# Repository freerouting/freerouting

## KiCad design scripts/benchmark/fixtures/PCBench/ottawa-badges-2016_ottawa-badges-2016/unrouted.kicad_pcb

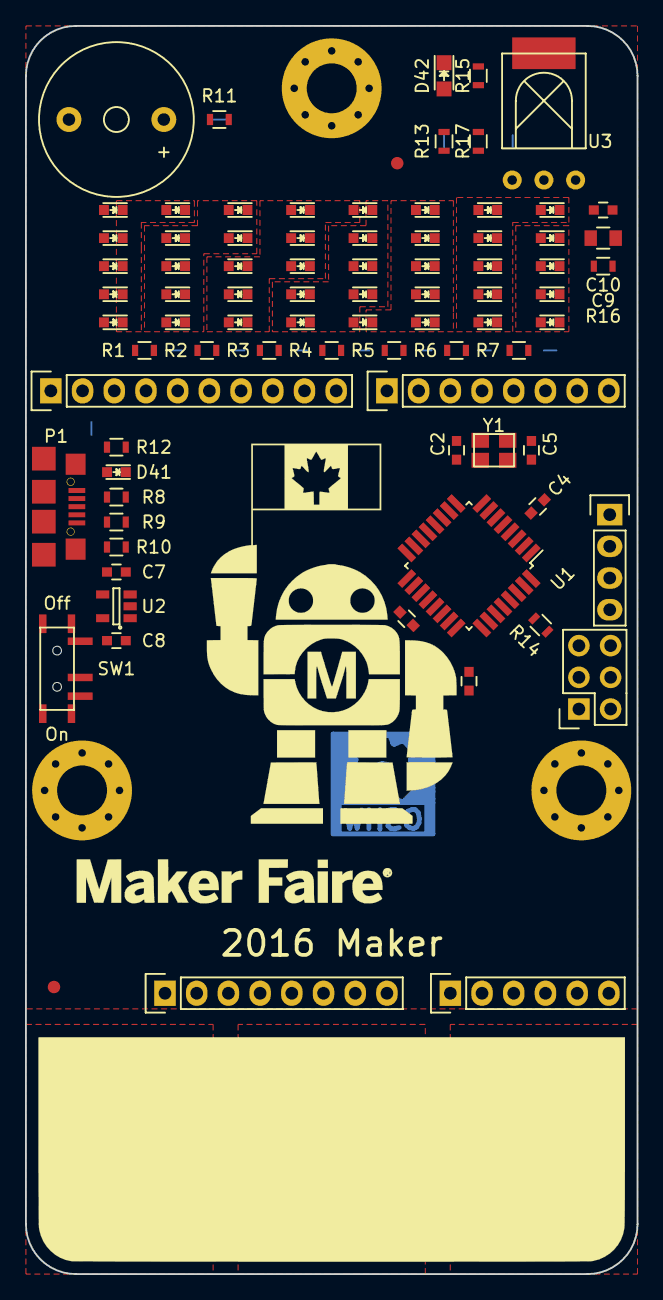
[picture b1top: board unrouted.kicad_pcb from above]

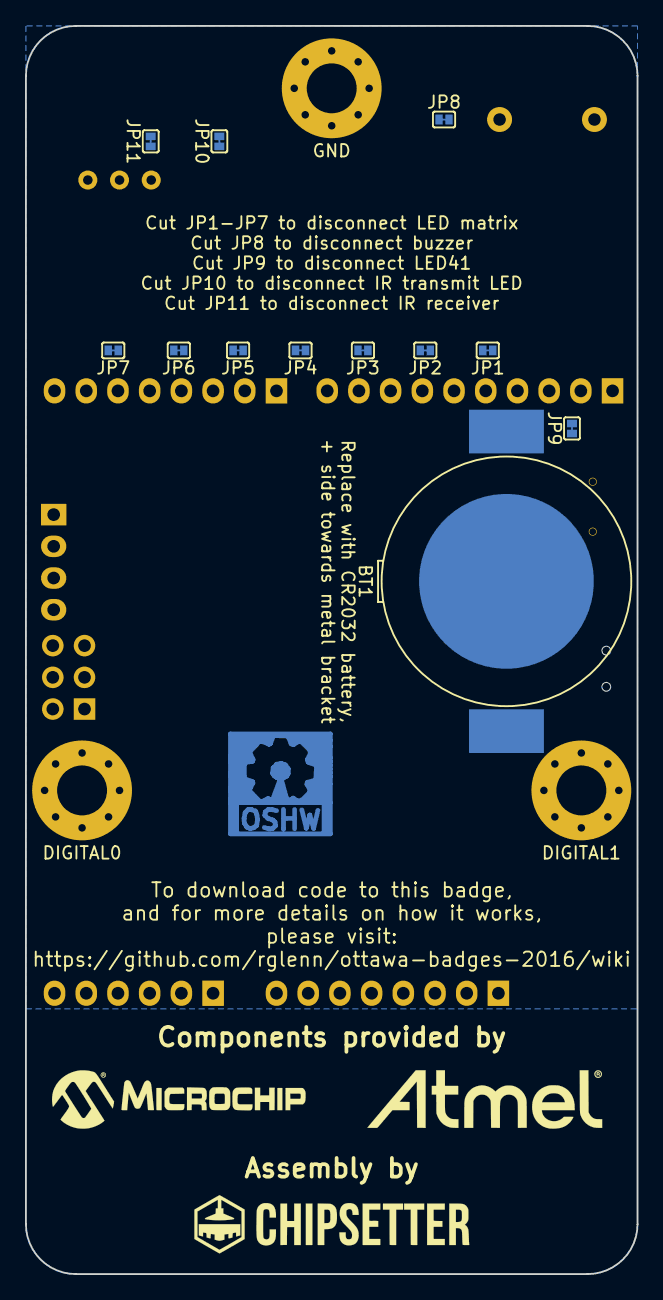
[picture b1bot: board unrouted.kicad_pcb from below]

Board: 2 copper layers, 49.0 x 100.0 mm, 96 parts (12 on the bottom side), 58 nets, no tracks yet.

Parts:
BT1: CR2032; CR2032-SHRAPNEL
C1, C4, C6, C10: 100n; C_0603
C2, C5: 18p; C_0603
C7, C8: 1u; C_0603
C9: 10u; C_0805
D1, D2, D3, D4, D5, D6, D7, D8, D9, D10, D11, D12, D13, D14, D15, D16, D17, D18, D19, D20, D21, D22, D23, D24, D25, D26, D27, D28, D29, D30, D31, D32, D33, D34, D35, D36, D37, D38, D39, D40, D41: Led_Small; LED_0603
D42: Led_Small; LED_0805
JP1, JP2, JP3, JP4, JP5, JP6, JP7, JP8, JP9, JP10, JP11: Jumper_NC_Small; SJ2
P1: USB_OTG; 10118192-0001LF
P2, P5: CONN_01X08; Socket_Strip_Straight_1x08
P3: CONN_01X06; Socket_Strip_Straight_1x06
P4: CONN_01X10; Socket_Strip_Straight_1x10
P6: CONN_02X03; Socket_Strip_Straight_2x03
P7, P8, P10: CONN_01X01; MountingHole_4mm_Pad_Via
P9: CONN_01X04; Socket_Strip_Straight_1x04
R1, R2, R3, R4, R5, R6, R7, R9, R10, R16: 56; R_0603
R8: 1.5K; R_0603
R11, R12, R13, R17: 1K; R_0603
R14, R15: 10K; R_0603
SP1: SPEAKER; Buzzer_12x9.5RM7.6
SW1: SWITCH_INV; MK-12C02
U1: ATMEGA328P-A; TQFP-32_7x7mm_Pitch0.8mm
U2: MIC5504-3.3YM5; SOT-23-5
U3: VS1838B; VS1838B-HORIZ
Y1: 12 MHz; crystal_FA238-TSX3225

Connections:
+3V3: C4.1, C6.1, P2.2, P2.4, P6.6, R14.2, R15.2, R16.2, SW1.2, U1.4, U1.18
+5V: C7.1, P1.1, P2.5, R8.1, U2.1, U2.3
/ANALOG0: P3.1, U1.23
/ANALOG1: P3.2, U1.24
/ANALOG2: P3.3, U1.25
/ANALOG3: JP7.1, P3.4, U1.26
/ANALOG4: JP8.1, P3.5, P4.2, U1.27
/ANALOG5: P3.6, P4.1, U1.28
/AREF: C1.1, P4.3, U1.20
/DIGITAL0: P5.8, P7.1, U1.30
/DIGITAL1: P5.7, P8.1, U1.31
/DIGITAL2: P5.6, R10.2, U1.32
/DIGITAL3: JP10.1, P5.5, U1.1
/DIGITAL4: JP6.1, P5.4, U1.2
/DIGITAL5: JP5.1, P5.3, U1.9
/DIGITAL6: JP4.1, P5.2, U1.10
/DIGITAL7: P5.1, R8.2, R9.2, U1.11
/DIGITAL8: JP3.1, P4.10, U1.12
/DIGITAL9: JP2.1, P4.9, U1.13
/DIGITAL10: JP1.1, P4.8, U1.14
/DIGITAL11: P4.7, P6.4, U1.15
/DIGITAL12: JP11.1, P4.6, P6.5, U1.16
/DIGITAL13: JP9.1, P4.5, P6.3, U1.17
/PE0: P9.1, U1.3
/PE1: P9.2, U1.6
/PE2: P9.3, U1.19
/PE3: P9.4, U1.22
/RESET: P2.3, P6.1, R14.1, U1.29
GND: BT1.2, C1.2, C2.2, C4.2, C5.2, C6.2, C7.2, C8.2, C9.2, C10.2, D41.1, D42.1, P1.5, P1.6, P2.6, P2.7, P4.4, P6.2, P10.1, SP1.2, U1.5, U1.21, U2.2, U3.2
unnamed: BT1.1, SW1.1
unnamed: C2.1, U1.8, Y1.1
unnamed: C5.1, U1.7, Y1.2
unnamed: C8.1, SW1.3, U2.5
unnamed: C9.1, C10.1, R16.1, U3.3
unnamed: D1.1, D2.1, D3.1, D4.1, D5.1, D6.1, D7.2, D13.2, D19.2, D25.2, D31.2, D37.2, R1.1
unnamed: D1.2, D7.1, D8.1, D9.1, D10.1, D11.1, D12.1, D14.2, D20.2, D26.2, D32.2, D38.2, R2.1
unnamed: D4.2, D10.2, D16.2, D22.2, D25.1, D26.1, D27.1, D28.1, D29.1, D30.1, D35.2, R5.1
unnamed: D5.2, D11.2, D17.2, D23.2, D29.2, D31.1, D32.1, D33.1, D34.1, D35.1, D36.1, R6.1
unnamed: D6.2, D12.2, D18.2, D24.2, D30.2, D36.2, D37.1, D38.1, D39.1, D40.1, R7.1
unnamed: D2.2, D8.2, D13.1, D14.1, D15.1, D16.1, D17.1, D18.1, D21.2, D27.2, D33.2, D39.2, R3.1
unnamed: D3.2, D9.2, D15.2, D19.1, D20.1, D21.1, D22.1, D23.1, D24.1, D28.2, D34.2, D40.2, R4.1
unnamed: D41.2, R12.1
unnamed: D42.2, R13.1
unnamed: JP1.2, R1.2
unnamed: JP2.2, R2.2
unnamed: JP3.2, R3.2
unnamed: JP4.2, R4.2
unnamed: JP5.2, R5.2
unnamed: JP6.2, R6.2
unnamed: JP7.2, R7.2
unnamed: JP8.2, R11.2
unnamed: JP9.2, R12.2
unnamed: JP10.2, R13.2
unnamed: JP11.2, R15.1, R17.2
unnamed: P1.2, R9.1
unnamed: P1.3, R10.1
unnamed: R11.1, SP1.1
unnamed: R17.1, U3.1

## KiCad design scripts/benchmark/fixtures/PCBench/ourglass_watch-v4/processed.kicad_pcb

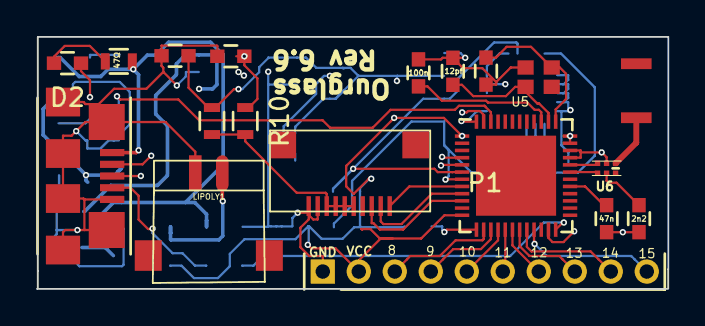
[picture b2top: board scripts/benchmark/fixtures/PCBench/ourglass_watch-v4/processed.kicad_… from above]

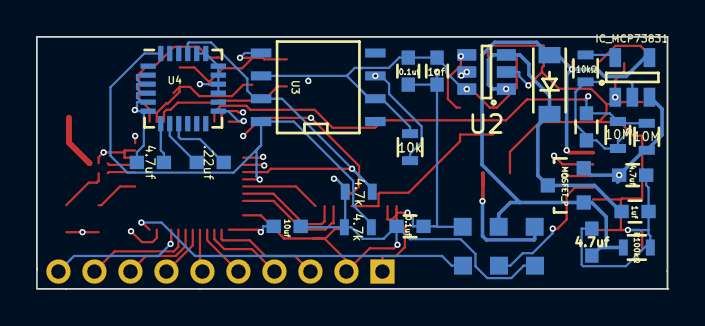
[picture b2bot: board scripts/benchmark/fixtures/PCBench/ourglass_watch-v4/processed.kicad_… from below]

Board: 4 copper layers, 35.1 x 14.0 mm, 43 parts (24 on the bottom side), 41 nets.

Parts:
ANT1: -; antenna
C1, C16, C17: 1uf; C_0603
C2, C3, C6: 4.7uf; C_0603
C4: 100n; C_0603
C5: .22uf; C_0603
C7: 10uf; C_0603
C8, C13: 0.1uf; C_0603
C9: 47n; C_0603
C10, C15: 12pf; C_0603
C11: 2n2; C_0603
C12: 1u; C_0603
C14: 1nf; C_0603
D1: DIODESCH; SOD-123
D2: LED; C_0603
J1: CONN_10; omron_XF2M-1015-1A-2
LIPOLY1: BATTERY; JST_2_pos
P1: Expansion Header; Pin_Header_Straight_1x10_Pitch2.00mm
P2: Test Points; test_points
Q1: MOSFET_P; SOT-23
R1: 47Ω; R_0603
R2: 10kΩ; R_0603
R3: R100kΩ; R_0603
R4: 10k; R_0603
R5, R6: 4.7k; R_0603
R7, R8: 10M; R_0603
R9, R10: 0; R_0603
U1: IC_MCP73831; SOT-23-5
U2: MIC5211; SOT-23-6
U3: DS3231; SOIC-8-N
U4: LSM9DS0; QFN-24-NO-CENTER4x4mm_Pitch0.5mm
U5: NRF51822; UQFN-48-1EP_6x6mm_Pitch0.4mm
U6: BALUN; BALUN-6
X1: 16mhz; SMD-Crystal
XL1: USB_MICRO_B; USB_Micro-B

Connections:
/5v_VCC: C17.1, R10.1, U2.4
/Accel_INT: U4.13, U5.48
/Bal1: U5.31, U6.4
/Bal2: U5.32, U6.3
/BatterySense: C12.1, R7.2, R8.1, U5.46
/ClockINT: R4.2, U3.3, U5.47
/Display_MOSI: J1.2, U5.9
/Display_SCK: J1.3, U5.10
/Display_SS: J1.1, U5.8
/EX8: P1.3, U5.14
/EX9: P1.4, U5.15
/EX10: P1.5, U5.16
/EX11: P1.6, U5.17
/EX12: P1.7, U5.18
/EX13: P1.8, U5.19
/EX14: P1.9, U5.20
/EX15: P1.10, U5.21
/EXTVCC: C2.1, D1.1, P2.5, Q1.1, R1.2, R3.1, U1.4, XL1.1
/RX: U5.5, XL1.3
/Regulator_In: C1.1, D1.2, Q1.3, U2.1, U2.3, U2.5
/Reset: P2.2, U5.23, XL1.4
/SCL: R5.1, U3.7, U4.21, U5.6
/SDA: R6.1, U3.8, U4.24, U5.7
/SWDCLK: P2.3, U5.24
/TX: U5.4, XL1.2
/VBAT: C3.1, LIPOLY1.2, P2.4, Q1.2, R7.1, U1.3
/VCC: C7.1, C8.1, C13.2, C14.2, C16.1, P1.2, P2.1, R4.1, R5.2, R6.2, R9.1, U2.6, U3.2, U3.6, U4.15, U4.16, U4.17, U4.18, U4.19, U4.20, U5.1, U5.12, U5.35, U5.36
/XC1: C10.1, U5.38, X1.3
/XC2: C15.1, U5.37, X1.1
GND: C1.2, C2.2, C3.2, C4.2, C6.2, C7.2, C8.2, C9.2, C10.2, C11.2, C12.2, C13.1, C14.1, C15.2, C16.2, C17.2, J1.9, J1.10, LIPOLY1.1, P1.1, P2.6, R2.2, R3.2, R8.2, U1.2, U2.2, U3.5, U4.2, U4.3, U4.4, U4.5, U4.6, U5.13, U5.33, U5.34, U6.2, X1.2, XL1.5
unnamed: ANT1.1, U6.1
unnamed: C4.1, U5.39
unnamed: C5.1, U4.9
unnamed: C5.2, U4.8
unnamed: C6.1, U4.7
unnamed: C9.1, U5.29
unnamed: C11.1, U6.5
unnamed: D2.1, U1.1
unnamed: D2.2, R1.1
unnamed: J1.5, J1.6, J1.7, J1.8, R9.2, R10.2
unnamed: R2.1, U1.5

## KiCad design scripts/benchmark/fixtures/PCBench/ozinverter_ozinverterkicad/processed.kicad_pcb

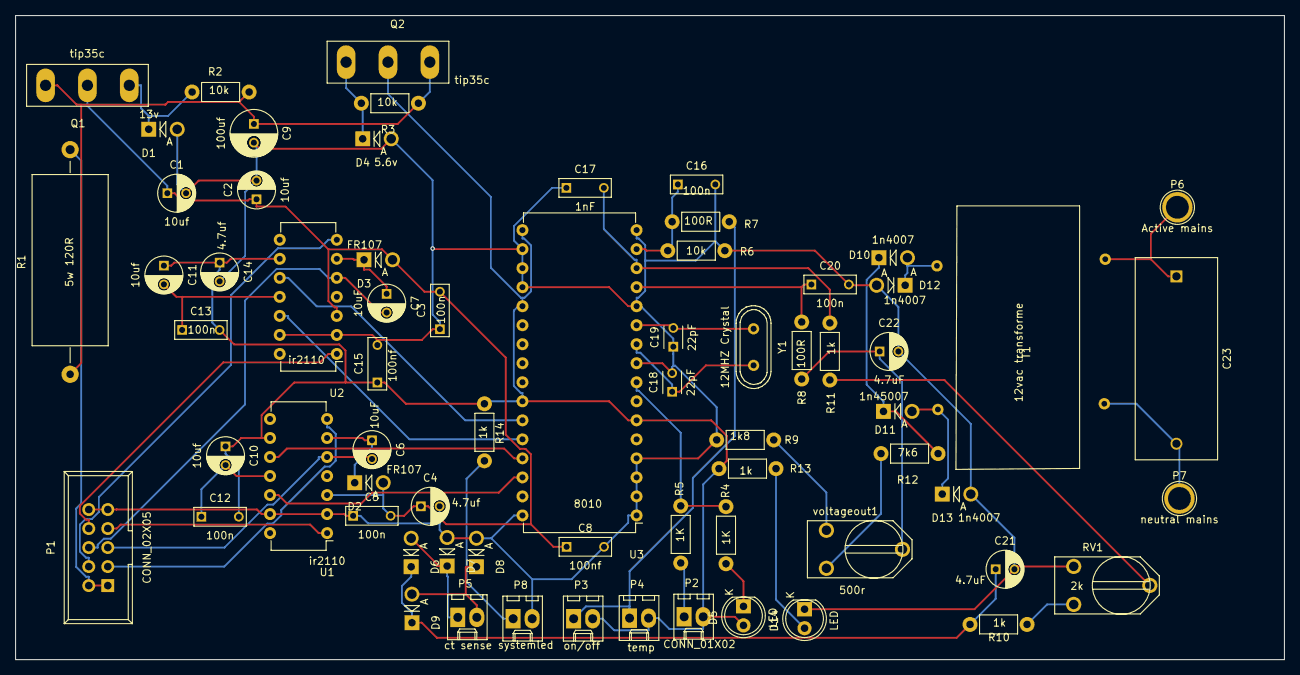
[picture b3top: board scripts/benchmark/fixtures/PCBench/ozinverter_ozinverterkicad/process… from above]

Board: 2 copper layers, 169.4 x 86.0 mm, 68 parts (0 on the bottom side), 45 nets.

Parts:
C1, C2: 10uf; C_Radial_D5_L6_P2.5
C3, C5, C12, C13, C16, C20: 100n; C_Rect_L7_W2.5_P5
C4, C14: 4.7uf; C_Radial_D5_L6_P2.5
C6, C7: 10uF; C_Radial_D5_L6_P2.5
C8, C15: 100nf; C_Rect_L7_W2.5_P5
C9: 100uf; C_Radial_D6.3_L11.2_P2.5
C10, C11: 10uf; C_Radial_D5_L11_P2.5
C17: 1nF; C_Rect_L7_W2.5_P5
C18, C19: 22pF; C_Disc_D3_P2.5
C21, C22: 4.7uF; C_Radial_D5_L6_P2.5
C23: 2uf; C_Rect_L27_W11_P22
D1: 13v; Diode_DO-41_SOD81_Vertical_AnodeUp
D2, D3: FR107; Diode_DO-41_SOD81_Vertical_AnodeUp
D4: 5.6v; Diode_DO-41_SOD81_Vertical_AnodeUp
D5, D14: LED; LED-5MM
D6, D7, D8, D9: D; Diode_DO-41_SOD81_Vertical_AnodeUp
D10, D12, D13: 1n4007; Diode_DO-41_SOD81_Vertical_AnodeUp
D11: 1n45007; Diode_DO-41_SOD81_Vertical_AnodeUp
P1: CONN_02X05; IDC_Header_Straight_10pins
P2: CONN_01X02; Molex_KK-6410-02_02x2.54mm_Straight
P3: on/off; Molex_KK-6410-02_02x2.54mm_Straight
P4: temp; Molex_KK-6410-02_02x2.54mm_Straight
P5: ct sense; Molex_KK-6410-02_02x2.54mm_Straight
P6: Active mains; 1pin
P7: neutral mains; 1pin
P8: systemled; Molex_KK-6410-02_02x2.54mm_Straight
Q1, Q2: tip35c; TO-247_Vertical_Neutral123
R1: 5w 120R; Resistor_Horizontal_RM30mm
R2, R3, R6: 10k; Resistor_Horizontal_RM7mm
R4, R5: 1K; Resistor_Horizontal_RM7mm
R7, R11: 100R; Resistor_Horizontal_RM7mm
R8, R10, R13, R14: 1k; Resistor_Horizontal_RM7mm
R9: 1k8; Resistor_Horizontal_RM7mm
R12: 7k6; Resistor_Horizontal_RM7mm
RV1: 2k; RV2X4
T1: 12vac transforme; 3wtransformer
U1, U2: ir2110; DIP-14_W7.62mm
U3: 8010; DIP-32_W15.24mm
Y1: 12MHZ Crystal; Crystal_HC49-U_Vertical
voltageout1: 500r; RV2X4

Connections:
+5V: C10.1, C11.1, C12.2, C13.2, C14.1, C15.1, D5.2, P2.2, P3.2, P4.2, Q2.2, R13.1, R14.1, U1.9, U2.9, U3.6, U3.17, U3.21, U3.26
+12V: C1.1, C2.1, C3.2, C4.1, C5.2, C8.1, D2.2, D3.2, Q1.2, U1.3, U2.3
+48V: P1.1, P1.2, R1.2
/24vin: C9.1, Q1.3, Q2.3, R1.1, R2.1, R3.1
GND: C1.2, C2.2, C3.1, C4.2, C5.1, C8.2, C9.2, C14.2, C15.2, C16.2, C17.1, C18.2, C19.1, C20.2, C21.2, C22.2, D1.2, D4.2, D7.2, D8.2, D12.2, D13.2, D14.1, P1.9, P1.10, P8.2, R6.2, R9.1, RV1.1, U1.2, U1.13, U2.2, U2.13, U3.1, U3.2, U3.3, U3.4, U3.9, U3.12, U3.16, U3.18, U3.19, U3.20, U3.32
unnamed: C6.1, D2.1, U1.6
unnamed: C6.2, P1.5, U1.5
unnamed: C7.1, D3.1, U2.6
unnamed: C7.2, P1.6, U2.5
unnamed: C10.2, C12.1, U1.11
unnamed: C11.2, C13.1, U2.11
unnamed: C16.1, R6.1, R7.2, U3.15
unnamed: C17.2, R8.2, U3.14
unnamed: C18.1, U3.10, Y1.2
unnamed: C19.2, U3.11, Y1.1
unnamed: C20.1, R11.1, U3.13
unnamed: C21.1, D6.1, D9.1, R10.1
unnamed: C22.1, R11.2, voltageout1.2
unnamed: C23.1, P6.1, T1.4
unnamed: C23.2, P7.1, T1.3
unnamed: D1.1, Q1.1, R2.2
unnamed: D4.1, Q2.1, R3.2
unnamed: D5.1, R4.2
unnamed: D6.2, D7.1, P5.1
unnamed: D8.1, D9.2, P5.2
unnamed: D10.1, D11.1, R12.1
unnamed: D10.2, D12.1, T1.2
unnamed: D11.2, D13.1, T1.1
unnamed: D14.2, R13.2
unnamed: P1.3, U1.7
unnamed: P1.4, U2.7
unnamed: P1.7, U1.1
unnamed: P1.8, U2.1
unnamed: P2.1, R5.2
unnamed: P3.1, P4.1, R7.1
unnamed: P8.1, R14.2
unnamed: R4.1, R5.1, U3.8
unnamed: R8.1, RV1.2
unnamed: R9.2, voltageout1.1
unnamed: R10.2, RV1.3
unnamed: R12.2, voltageout1.3
unnamed: U1.10, U3.29
unnamed: U1.12, U3.30
unnamed: U2.10, U3.27
unnamed: U2.12, U3.28

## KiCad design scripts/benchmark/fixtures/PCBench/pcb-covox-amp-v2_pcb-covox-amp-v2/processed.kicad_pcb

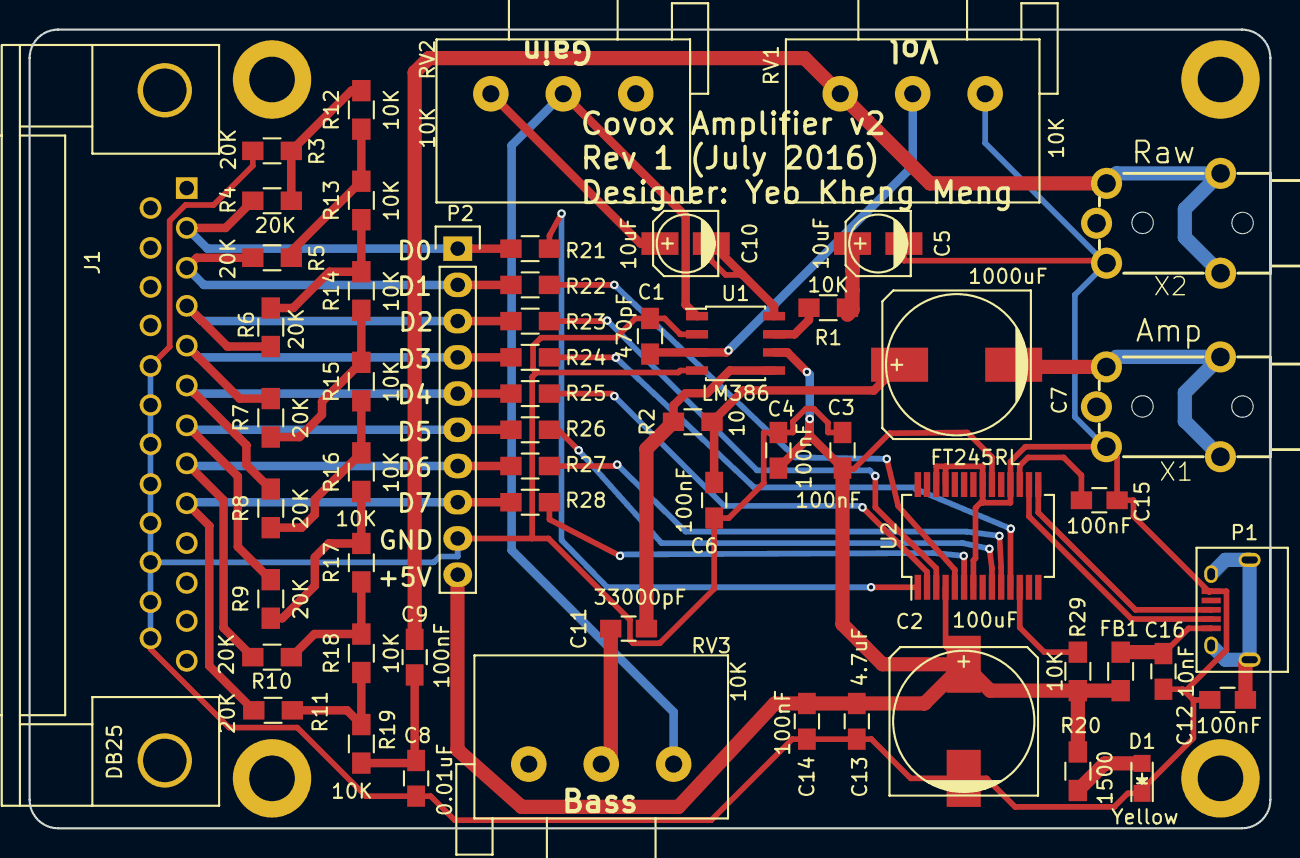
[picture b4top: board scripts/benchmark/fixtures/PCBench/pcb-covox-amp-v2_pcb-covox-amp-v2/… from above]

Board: 2 copper layers, 87.0 x 56.0 mm, 61 parts (0 on the bottom side), 45 nets.

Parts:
C1: 470pF; C_0805_HandSoldering
C2: 100uF; c_elec_10x10.5
C3, C4, C6, C9, C12, C14, C15: 100nF; C_0805_HandSoldering
C5, C10: 10uF; c_elec_4x5.3
C7: 1000uF; c_elec_10x10.5
C8: 0.01uF; C_0805_HandSoldering
C11: 33000pF; C_0805_HandSoldering
C13: 4.7uF; C_0805_HandSoldering
C16: 10nF; C_0805_HandSoldering
D1: Yellow; LED_0805
FB1: FERRITE; R_0805_HandSoldering
J1: DB25; DB25MC
MH1, MH2, MH3, MH4: MOUNTHOLE; MountingHole_3.2mm_M3_ISO14580_Pad
P1: USB; USB_Micro-B
P2: CONN_01X10; Pin_Header_Straight_1x10
R1, R12, R13, R14, R15, R16, R17, R18, R19, R29: 10K; R_0805_HandSoldering
R2: 10; R_0805_HandSoldering
R3, R4, R5, R6, R7, R8, R9, R10, R11: 20K; R_0805_HandSoldering
R20: 1500; R_0805_HandSoldering
R21, R22, R23, R24, R25, R26, R27, R28: 100; R_0805_HandSoldering
RV1, RV2, RV3: 10K; Potentiometer_Alps-RK163-single_15mm
U1: LM386; SOIC-8_3.9x4.9mm_Pitch1.27mm
U2: FT245RL; SSOP-28_5.3x10.2mm_Pitch0.65mm
X1: Amp; mj-2135-MJ-2135
X2: Raw; mj-2135-MJ-2135

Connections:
+5V: C2.1, C3.1, C4.1, C13.1, C14.1, FB1.2, P2.10, R20.1, R29.1, U1.6, U2.4, U2.20
Amp-Audio: C7.2, X1.P$3, X1.P$4, X1.P$5
Data0: J1.2, P2.1, R4.2, R21.1
Data1: J1.3, P2.2, R5.2, R22.1
Data2: J1.4, P2.3, R6.2, R23.1
Data3: J1.5, P2.4, R7.2, R24.1
Data4: J1.6, P2.5, R8.2, R25.1
Data5: J1.7, P2.6, R9.2, R26.1
Data6: J1.8, P2.7, R10.2, R27.1
Data7: J1.9, P2.8, R11.2, R28.1
GND: C1.1, C2.2, C3.2, C4.2, C5.2, C6.2, C8.2, C12.1, C13.2, C14.2, C15.2, C16.2, D1.1, J1.18, J1.19, J1.20, J1.21, J1.22, J1.23, J1.24, J1.25, P1.5, P2.9, R3.2, RV1.1, U1.2, U1.4, U2.7, U2.18, U2.21, U2.25, U2.26, X1.P$2, X2.P$2
Gain1: RV2.2, RV3.3, U1.1
Gain8: C10.2, U1.8
Input+: C1.2, RV1.2, U1.3
unnamed: C5.1, R1.1
unnamed: C6.1, C7.1, R2.1
unnamed: C8.1, C9.1, R19.1
unnamed: C10.1, RV2.3
unnamed: C11.2, RV3.2
unnamed: C12.2, P1.6
unnamed: C15.1, U2.17
unnamed: C16.1, FB1.1, P1.1
unnamed: D1.2, R20.2
unnamed: R1.2, U1.7
unnamed: R10.1, R17.1, R18.2
unnamed: R11.1, R18.1, R19.2
unnamed: R5.1, R12.1, R13.2
unnamed: R3.1, R4.1, R12.2
unnamed: R6.1, R13.1, R14.2
unnamed: R7.1, R14.1, R15.2
unnamed: R8.1, R15.1, R16.2
unnamed: R9.1, R16.1, R17.2
unnamed: R21.2, U2.1
unnamed: R22.2, U2.5
unnamed: R23.2, U2.3
unnamed: R24.2, U2.11
unnamed: R25.2, U2.2
unnamed: R26.2, U2.9
unnamed: R27.2, U2.10
unnamed: R28.2, U2.6
unnamed: R29.2, U2.12
Source-Audio: C9.2, RV1.3, X2.P$3, X2.P$4, X2.P$5
USB_D+: P1.3, U2.15
USB_D-: P1.2, U2.16
Vout: C11.1, R2.2, U1.5
